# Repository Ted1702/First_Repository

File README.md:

# First_Repository
This is the first time i use git

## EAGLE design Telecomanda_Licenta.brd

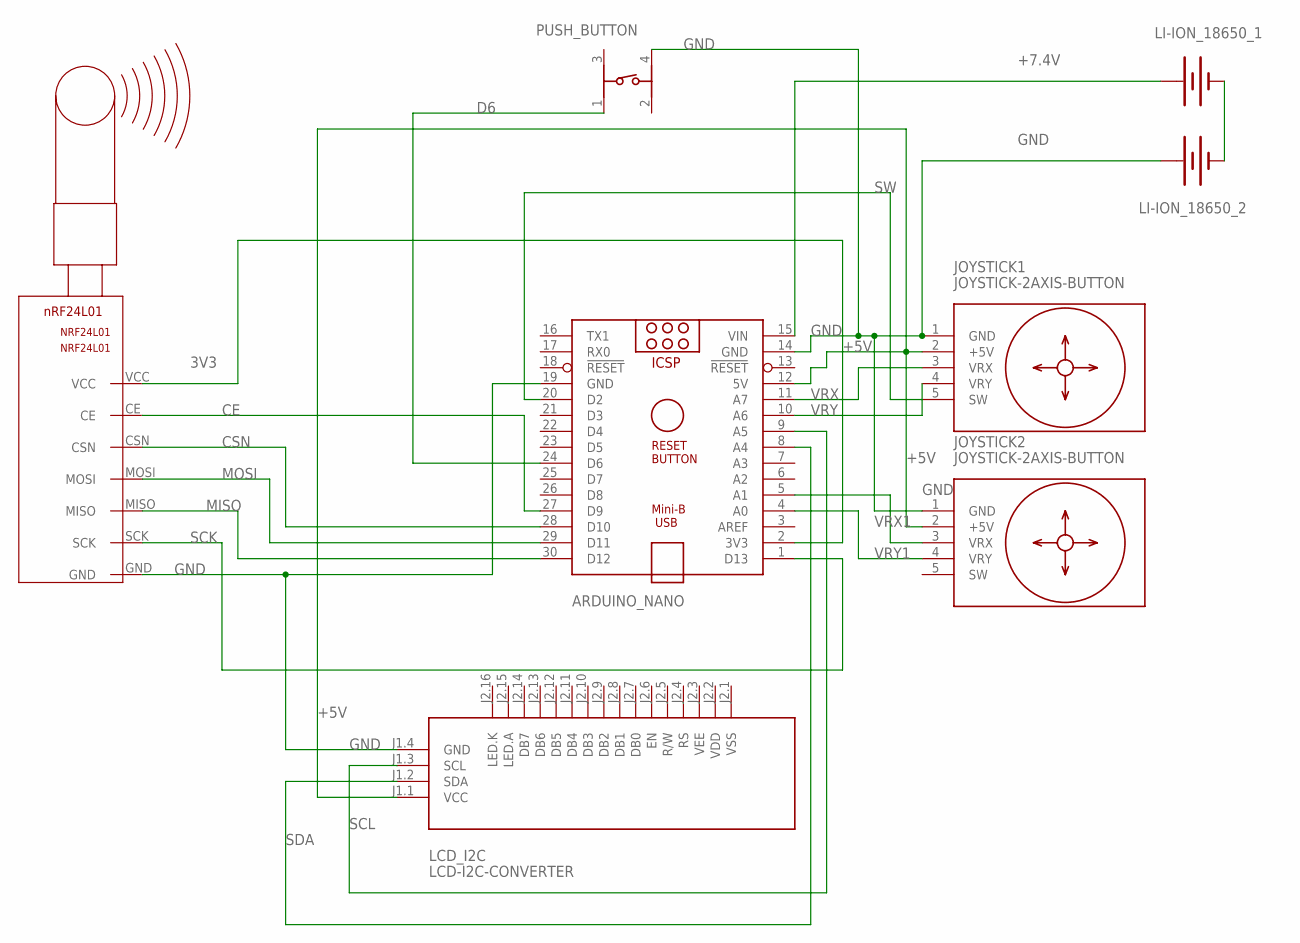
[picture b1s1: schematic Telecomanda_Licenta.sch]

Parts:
ARDUINO_NANO: ARDUINO_NANO
JOYSTICK1, JOYSTICK2: JOYSTICK-2AXIS-BUTTON
LCD_I2C: LCD-I2C-CONVERTER
LI-ION_18650_1, LI-ION_18650_2: BATTERY-18650; BATTERY_18650-HOLDER
NRF24L01: NRF24L01
PUSH_BUTTON: 430152050836

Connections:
3V3: ARDUINO_NANO.2 (3V3), NRF24L01.VCC
+5V: ARDUINO_NANO.12 (5V), JOYSTICK1.2 (+5V), JOYSTICK2.2 (+5V), LCD_I2C.J1.1 (VCC)
+7.4V: ARDUINO_NANO.15 (VIN), LI-ION_18650_1.PWR@1 (+)
CE: ARDUINO_NANO.27 (D9), NRF24L01.CE
CSN: ARDUINO_NANO.28 (D10), NRF24L01.CSN
D6: ARDUINO_NANO.24 (D6), PUSH_BUTTON.1
GND: ARDUINO_NANO.14 (GND), ARDUINO_NANO.19 (GND), JOYSTICK1.1 (GND), JOYSTICK2.1 (GND), LCD_I2C.J1.4 (GND), LI-ION_18650_2.PWR@1 (+), NRF24L01.GND, PUSH_BUTTON.4
MISO: ARDUINO_NANO.30 (D12), NRF24L01.MISO
MOSI: ARDUINO_NANO.29 (D11), NRF24L01.MOSI
unnamed: LI-ION_18650_1.GND@1 (-), LI-ION_18650_2.GND@1 (-)
SCK: ARDUINO_NANO.1 (D13), NRF24L01.SCK
SCL: ARDUINO_NANO.9 (A5), LCD_I2C.J1.3 (SCL)
SDA: ARDUINO_NANO.8 (A4), LCD_I2C.J1.2 (SDA)
SW: ARDUINO_NANO.20 (D2), JOYSTICK1.5 (SW)
VRX: ARDUINO_NANO.11 (A7), JOYSTICK1.3 (VRX)
VRX1: ARDUINO_NANO.5 (A1), JOYSTICK2.3 (VRX)
VRY: ARDUINO_NANO.10 (A6), JOYSTICK1.4 (VRY)
VRY1: ARDUINO_NANO.4 (A0), JOYSTICK2.4 (VRY)

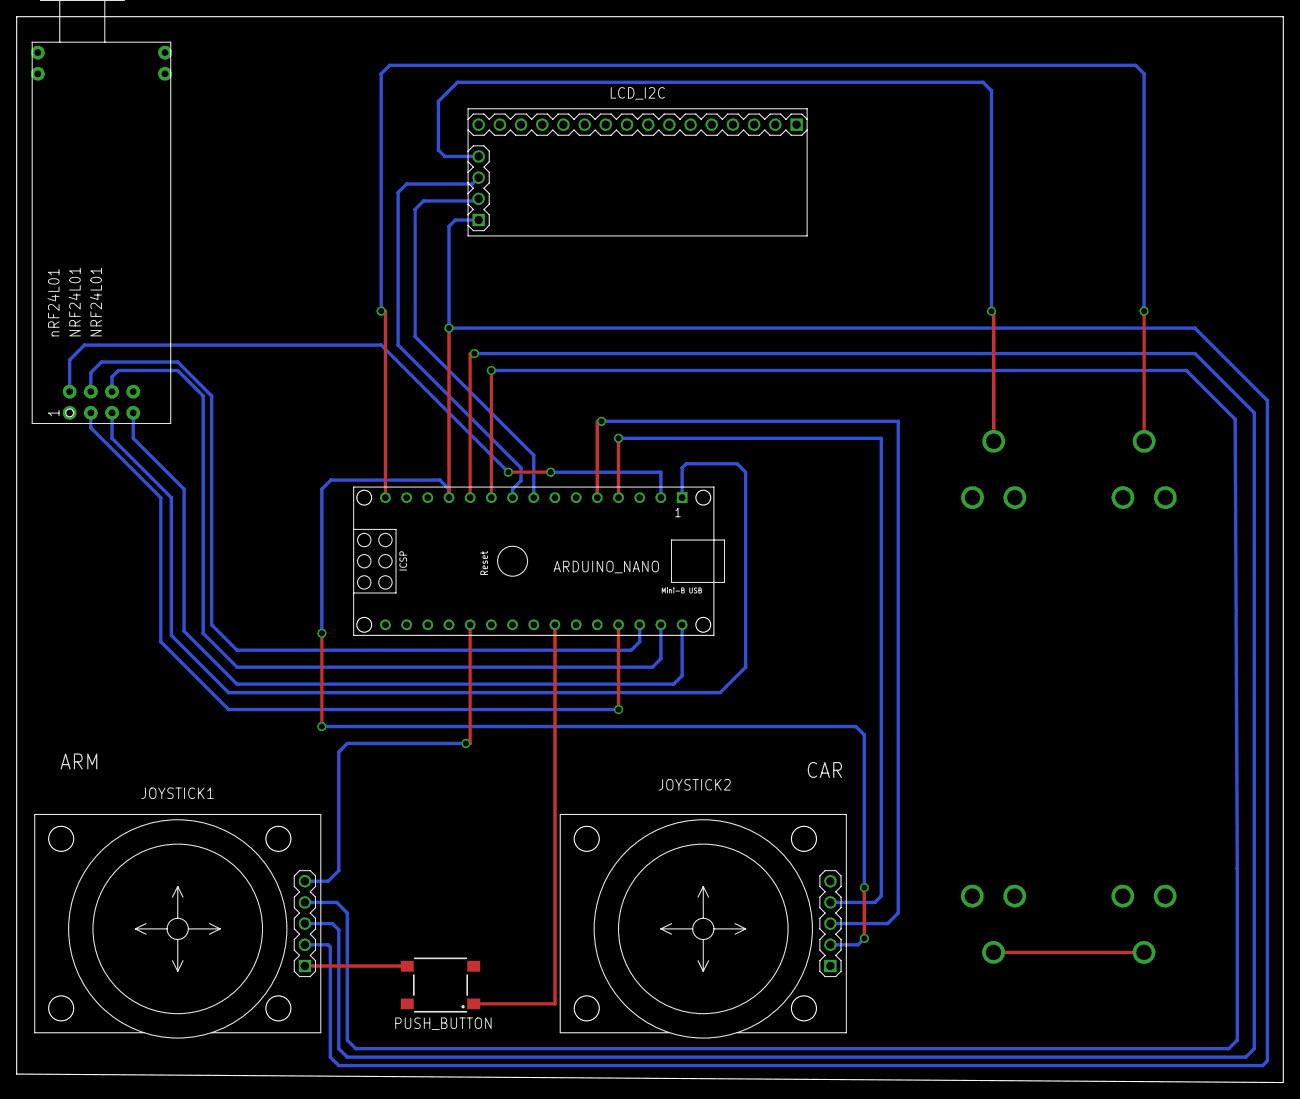
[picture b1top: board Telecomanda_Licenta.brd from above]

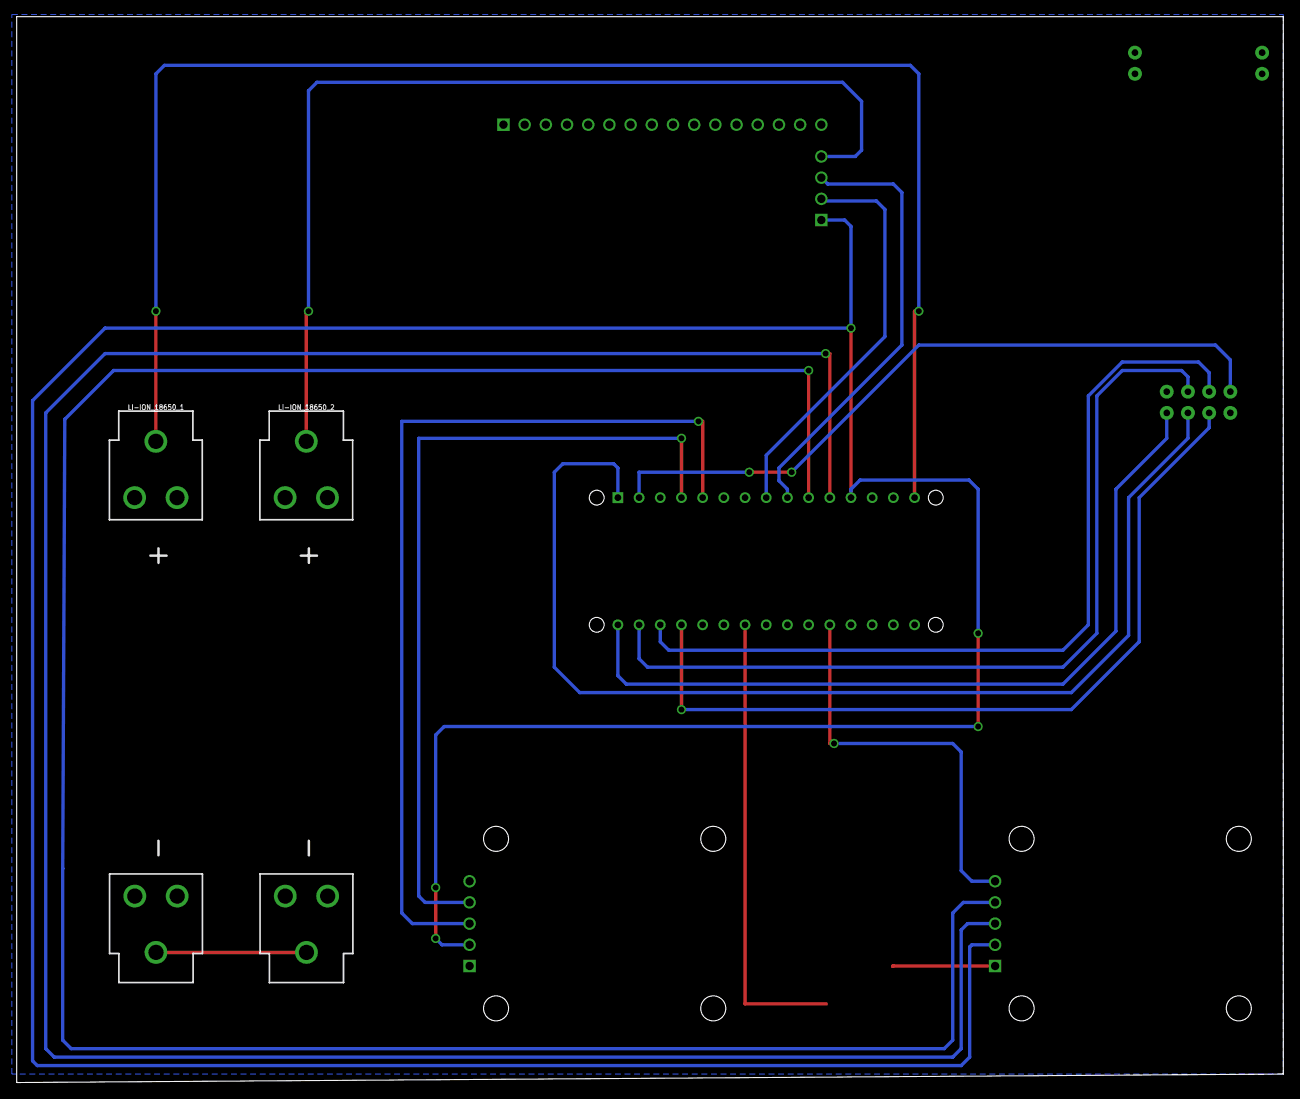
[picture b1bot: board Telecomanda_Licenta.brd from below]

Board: 2 copper layers, 151.8 x 127.8 mm, 8 parts (2 on the bottom side), 18 nets.

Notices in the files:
parts and their libraries:
diy-modules: Released under the Creative Commons Attribution 4.0 International License: http://creativecommons.org/licenses/by/4.0
Wurth_Switch_WS-TASV: Copyright: Würth Elektronik
